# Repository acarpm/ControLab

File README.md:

## Fonctionnement de la carte ControlLab

### Vue d'ensemble

ControlLab est une carte de contrôle d'accès NFC.
Son rôle est de lire un badge NFC présenté par un utilisateur,
de vérifier son autorisation, puis de signaler le résultat
(LED + buzzer). 

```
Badge NFC
    │
    ▼
┌─────────┐    I2C     ┌──────────────────┐
│  PN532  │ ────────▶  │  ESP32-S3-MINI-1 │
│  (NFC)  │            │                  │
└─────────┘            │  • Lecture UID   │
                       │  • Vérification  │
┌─────────┐            │  • Wi-Fi / BLE   │
│  OLED   │ ◀───I2C─── │                  │
└─────────┘            └──────────────────┘
                              │        │
                         GPIO38    GPIO46
                              │        │
                        NeoPixels   Buzzer
```
                
### 1. Alimentation

La carte est alimentée via USB-C (VBUS = 5V).

- **Polyfuse F1** : protection contre les surintensités
- **TVS D6** : protection contre les surtensions ESD sur VBUS
- **AMS1117-3.3** : régulateur linéaire qui abaisse le 5V en 3.3V
  pour alimenter l'ESP32, le PN532, l'OLED et le buzzer.

USB-C (5V VBUS)
    │
   [F1] Polyfuse
    │
   [D6] TVS (protection ESD)
    │
[AMS1117-3.3] ──▶ 3V3 (ESP32, PN532, OLED, Buzzer)

### 2. Lecture NFC (PN532)

Le module PN532 est le lecteur NFC de la carte.
Il communique avec l'ESP32 via **I2C** (SDA = GPIO10, SCL = GPIO11).

Quand un badge ( tag NFC) est présenté :
1. Le PN532 détecte le champ RF et lit l'**UID** du badge
2. Il transmet l'UID à l'ESP32 via I2C

Les lignes RSTPD (GPIO11) et IRQ (GPIO10) permettent
à l'ESP32 de réinitialiser le PN532 et d'être notifié
d'une nouvelle lecture sans polling continu.

### 3. Signalisation utilisateur

#### LEDs NeoPixel (GPIO38)
3 LEDs RGB WS2812 montées en chaîne DIN → DOUT.
Elles indiquent l'état de la lecture :

| Couleur       | Signification         |
|---------------|-----------------------|
| 🟢 Vert       | Accès autorisé        |
| 🔴 Rouge      | Accès refusé          |
| 🔵 Bleu       | En attente / veille   |

#### Buzzer (GPIO46)
Buzzer actif 3.3V piloté via GPIO46 (R7 = 200Ω en série).
- 1 bip court : badge reconnu
- 2 bips : accès refusé

#### Écran OLED (J2 — I2C)
Affiche le nom de l'utilisateur ou le statut de la carte.
Lignes I2C partagées avec le PN532 .
Pull-ups 4.7kΩ maintenus à 3.3V (R5, R6).

### 5. Programmation

La carte se programme via **USB natif** (GPIO18/19 — USB D-/D+).
Aucun adaptateur UART externe nécessaire.
Pour passer en mode flash :
1. Maintenir **BOOT** (SW2 — GPIO0)
2. Appuyer sur **RESET** (SW1)
3. Relâcher BOOT

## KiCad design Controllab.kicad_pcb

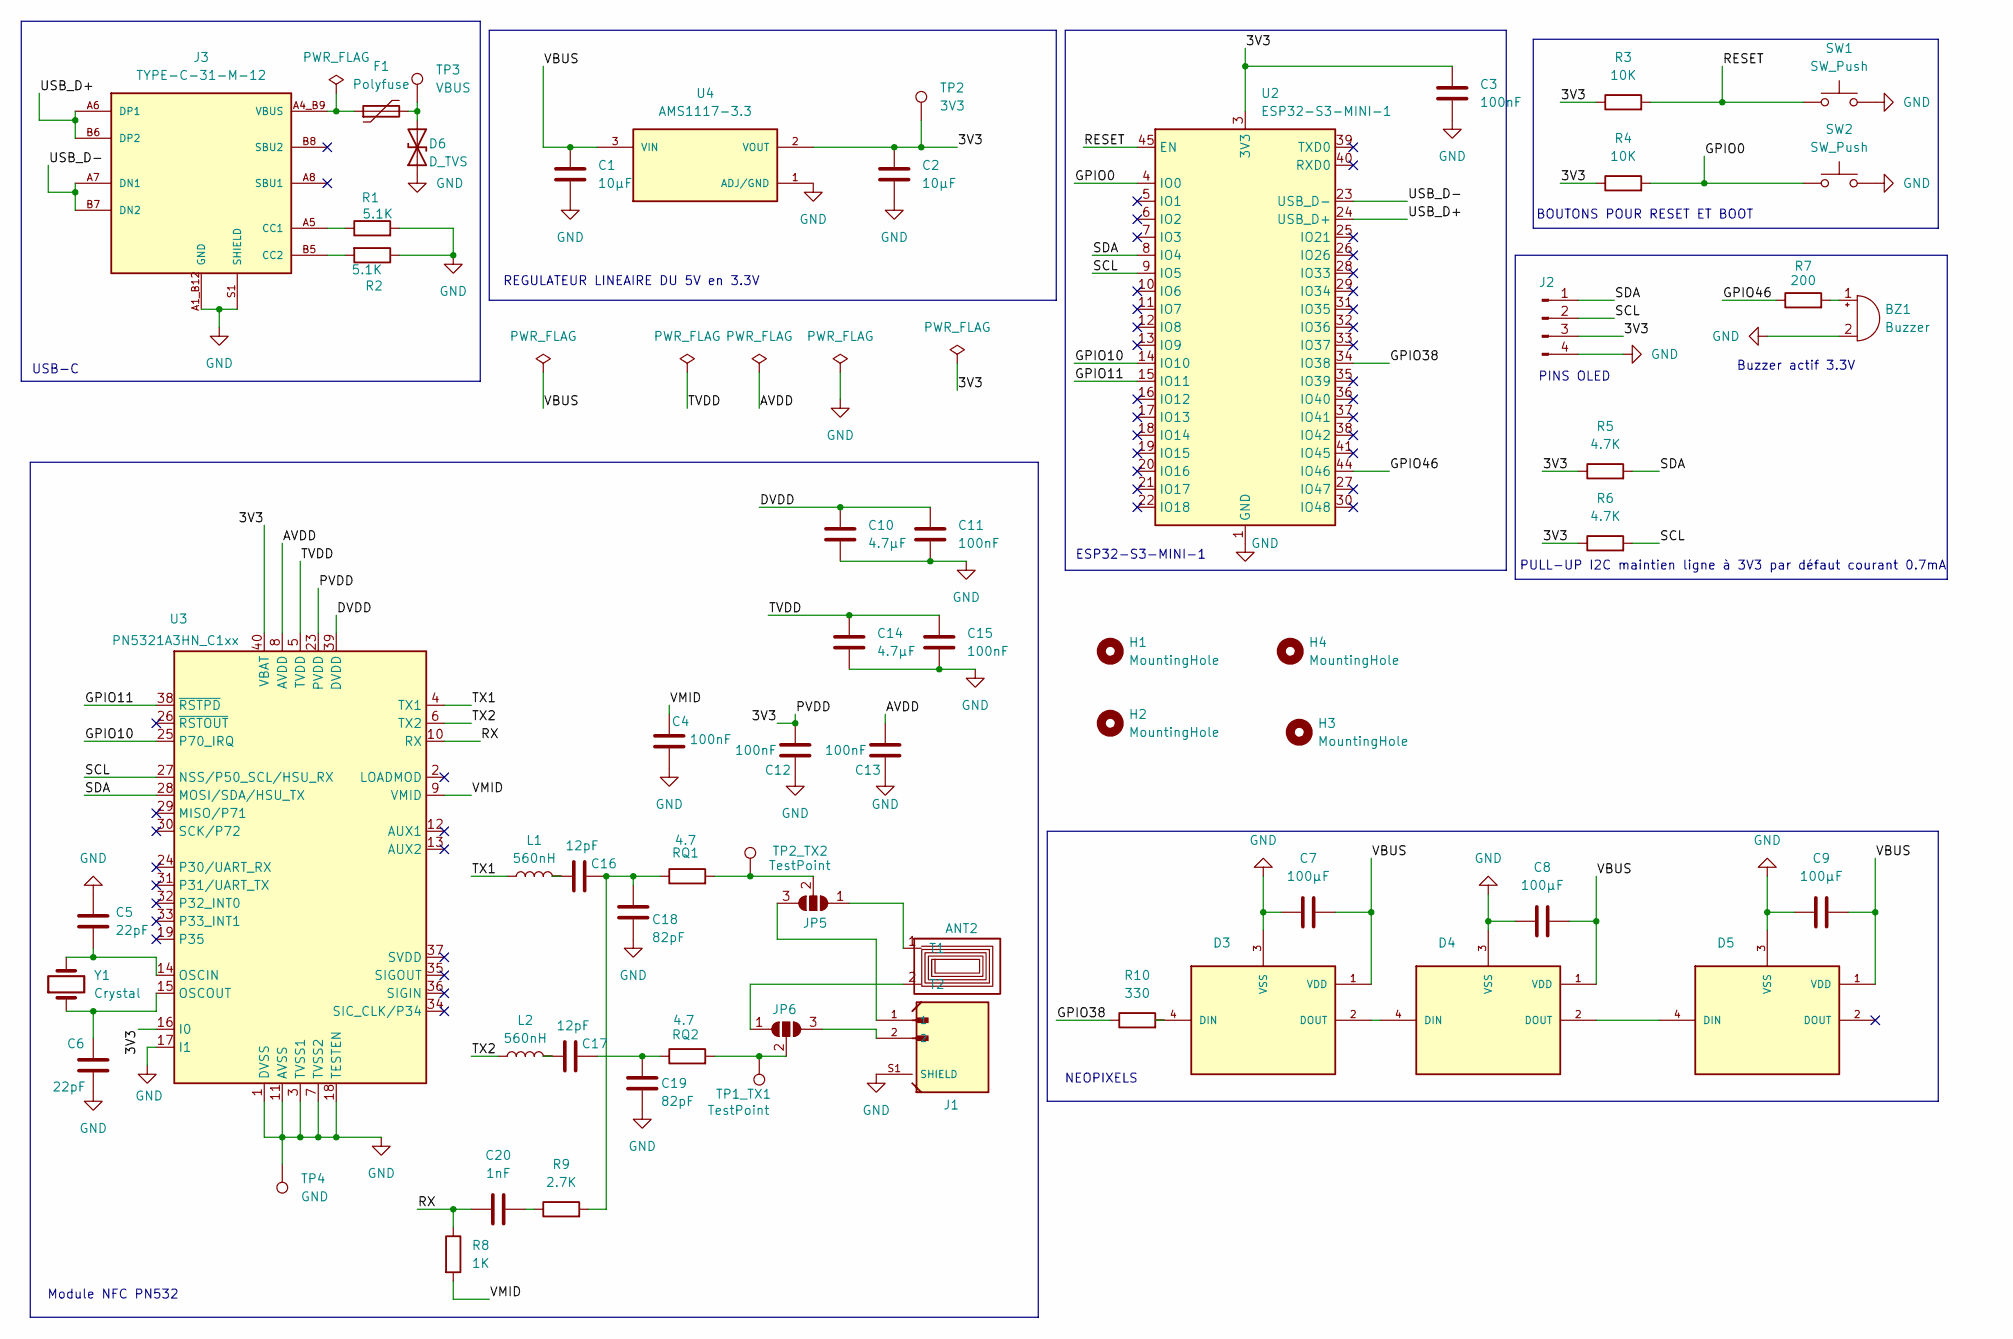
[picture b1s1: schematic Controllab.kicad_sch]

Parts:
ANT2: 13.56MHz_NFC_Antenna_Square; NFC_35x20_N5_NXP_PN532
BZ1: Buzzer; Buzzer_12x9.5RM7.6
C1, C2: 10µF; C_0603_1608Metric
C3, C4, C11, C12, C13, C15: 100nF; C_0603_1608Metric
C5, C6: 22pF; C_0603_1608Metric
C7, C8, C9: 100µF; C_0603_1608Metric
C10, C14: 4.7µF; C_0603_1608Metric
C16, C17: 12pF; C_0603_1608Metric
C18, C19: 82pF; C_0603_1608Metric
C20: 1nF; C_0603_1608Metric
D3, D4, D5: 2758; SOL320P540X170-4N; PARTREV 01
D6: D_TVS; D_SOD-123
F1: Polyfuse; Fuse_1206_3216Metric
H1, H2, H3, H4: MountingHole; MountingHole_2.1mm
J1: BM02B-GHS-TBT_LF__SN__N_; JST_BM02B-GHS-TBT_LF__SN__N_
J2: PinHeader_1x04_P2.54mm_Vertical
J3: TYPE-C-31-M-12; HRO_TYPE-C-31-M-12; PARTREV 2020.12.08
JP5, JP6: SolderJumper_3_Open; SolderJumper-3_P1.3mm_Open_Pad1.0x1.5mm
L1, L2: 560nH; L_0603_1608Metric
R1, R2: 5.1K; R_0603_1608Metric
R3, R4: 10K; R_0603_1608Metric
R5, R6: 4.7K; R_0603_1608Metric
R7: 200; R_0603_1608Metric
R8: 1K; R_0603_1608Metric
R9: 2.7K; R_0603_1608Metric
R10: 330; R_0603_1608Metric
RQ1, RQ2: 4.7; R_0603_1608Metric
SW1, SW2: SW_Push; SW_SPST_PTS645Sx43SMTR92
TP1_TX1, TP2_TX2: TestPoint; TestPoint_Pad_D1.0mm
TP2: 3V3; TestPoint_Pad_D1.0mm
TP3: VBUS; TestPoint_Pad_D1.0mm
TP4: GND; TestPoint_Pad_D1.0mm
U2: ESP32-S3-MINI-1; XCVR_ESP32-S3-MINI-1-N8
U3: PN5321A3HN_C1xx; HVQFN-40-1EP_6x6mm_P0.5mm_EP4.1x4.1mm
U4: AMS1117-3.3; SOT229P700X180-4N; PARTREV NA
Y1: Crystal; Crystal_SMD_3225-4Pin_3.2x2.5mm

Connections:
/3V3: C2.1, C3.1, C12.1, J2.3, R3.1, R4.1, R5.1, R6.1, TP2.1 (1_1), U2.3 (3V3), U3.16 (I0), U3.23 (PVDD), U3.40 (VBAT), U4.2 (VOUT)
/AVDD: C13.1, U3.8 (AVDD)
/DVDD: C10.2, C11.2, U3.39 (DVDD)
/GPIO0: R4.2, SW2.1, U2.4 (IO0)
/GPIO10: U2.14 (IO10), U3.25 (P70_IRQ)
/GPIO11: U2.15 (IO11), U3.38 (~RSTPD)
/GPIO38: R10.1, U2.34 (IO38)
/GPIO46: R7.1, U2.44 (IO46)
/RESET: R3.2, SW1.1, U2.45 (EN)
/RX: C20.1, R8.1, U3.10 (RX)
/SCL: J2.2, R6.2, U2.9 (IO5), U3.27 (NSS/P50_SCL/HSU_RX)
/SDA: J2.1, R5.2, U2.8 (IO4), U3.28 (MOSI/SDA/HSU_TX)
/TVDD: C14.2, C15.2, U3.5 (TVDD)
/TX1: L1.1, U3.4 (TX1)
/TX2: L2.1, U3.6 (TX2)
/USB_D+: J3.A6 (DP1), J3.B6 (DP2), U2.24 (USB_D+)
/USB_D-: J3.A7 (DN1), J3.B7 (DN2), U2.23 (USB_D-)
/VMID: C4.1, R8.2, U3.9 (VMID)
GND: BZ1.2 (-), C1.2, C2.2, C3.2, C4.2, C5.2, C6.2, C7.1, C8.1, C9.1, C10.1, C11.1, C12.2, C13.2, C14.1, C15.1, C18.2, C19.2, D3.3 (VSS), D4.3 (VSS), D5.3 (VSS), D6.1 (A1), J1.S1 (SHIELD), J1.S2 (SHIELD), J2.4, J3.A1_B12 (GND), J3.S1 (SHIELD), R1.2, R2.1, SW1.2, SW2.2, TP4.1 (1_1), U2.1 (GND), U2.2 (GND), U2.42 (GND), U2.43 (GND), U2.46 (GND), U2.47 (GND), U2.48 (GND), U2.49 (GND), U2.50 (GND), U2.51 (GND), U2.52 (GND), U2.53 (GND), U2.54 (GND), U2.55 (GND), U2.56 (GND), U2.57 (GND), U2.58 (GND), U2.59 (GND), U2.60 (GND), U2.61 (GND), U2.62 (GND), U2.63 (GND), U2.64 (GND), U2.65 (GND), U3.1 (DVSS), U3.3 (TVSS1), U3.7 (TVSS2), U3.11 (AVSS), U3.17 (I1), U3.18 (TESTEN), U3.41 (AVSS), U4.1 (ADJ/GND); also elsewhere on the board
unnamed: ANT2.1 (T1), JP5.1 (A)
unnamed: ANT2.2 (T2), JP6.1 (A)
unnamed: BZ1.1 (+), R7.2
unnamed: C16.1, L1.2
unnamed: C16.2, C18.1, R9.2, RQ1.1
unnamed: C17.1, L2.2
unnamed: C17.2, C19.1, RQ2.1
unnamed: C20.2, R9.1
unnamed: D3.4 (DIN), R10.2
unnamed: D3.2 (DOUT), D4.4 (DIN)
unnamed: D4.2 (DOUT), D5.4 (DIN)
unnamed: D6.2 (A2), F1.2, TP3.1 (1_1)
unnamed: J3.A5 (CC1), R1.1
unnamed: J3.B5 (CC2), R2.2
unnamed: J1.1, JP5.3 (B)
unnamed: JP5.2 (C), RQ1.2, TP2_TX2.1 (1_1)
unnamed: J1.2, JP6.3 (B)
unnamed: JP6.2 (C), RQ2.2, TP1_TX1.1 (1_1)
unnamed: C5.1, U3.14 (OSCIN), Y1.2
unnamed: C6.1, U3.15 (OSCOUT), Y1.1

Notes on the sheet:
Buzzer actif 3.3V
PINS OLED
NEOPIXELS
Module NFC PN532
ESP32-S3-MINI-1
REGULATEUR LINEAIRE DU 5V en 3.3V
USB-C
BOUTONS POUR RESET ET BOOT
PULL-UP I2C maintien ligne à 3V3 par défaut courant 0.7mA

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
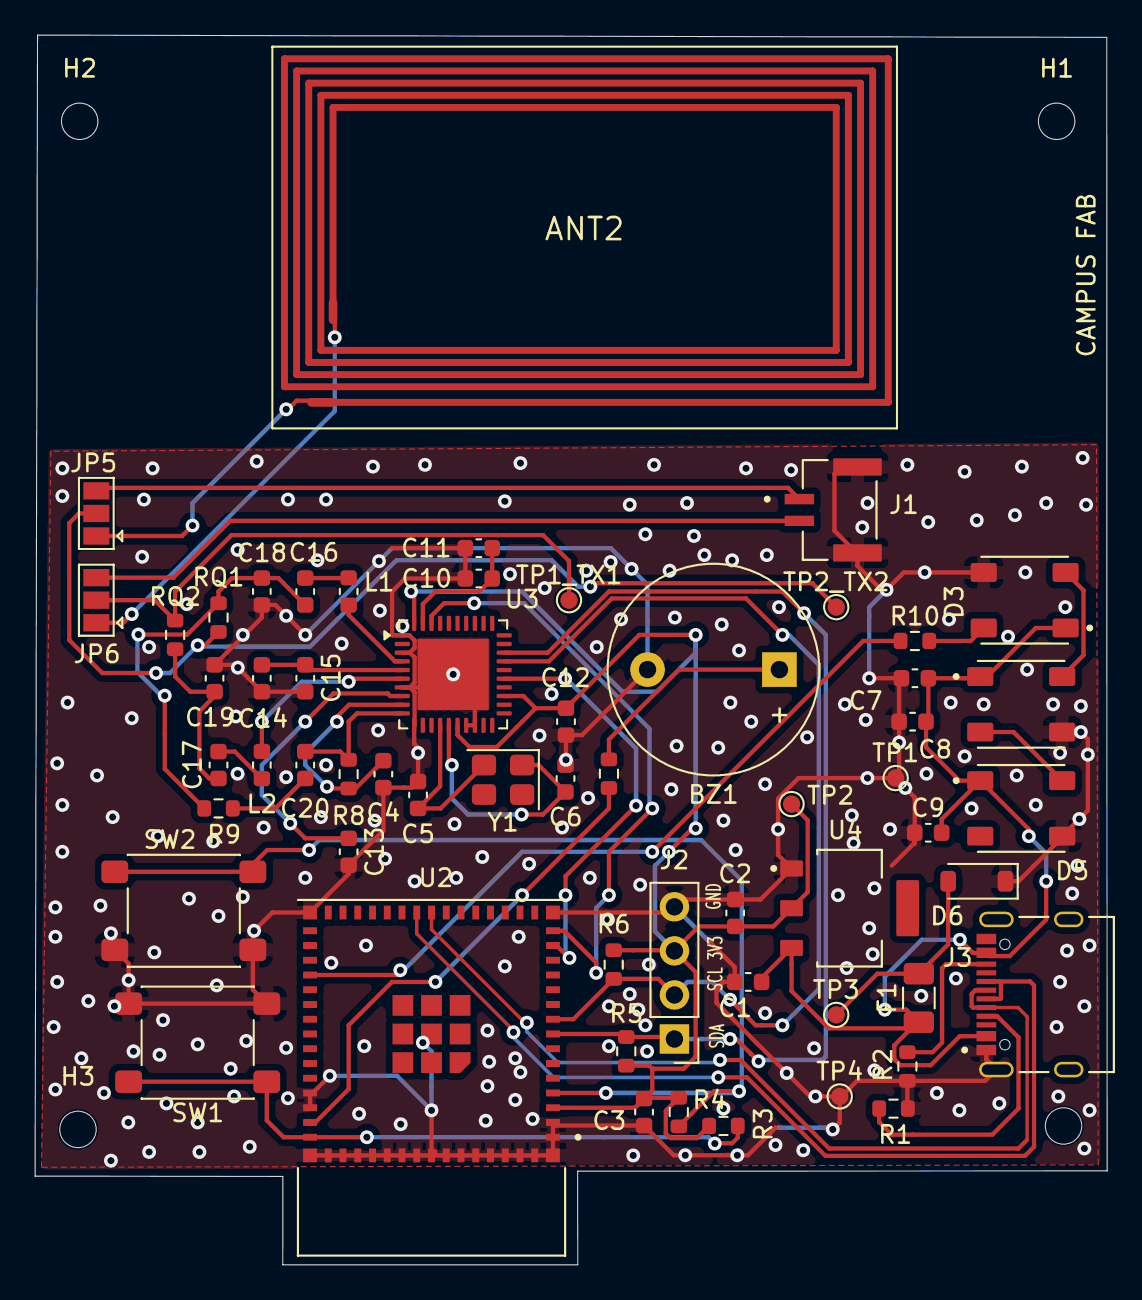
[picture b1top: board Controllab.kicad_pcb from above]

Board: 2 copper layers, 61.8 x 70.9 mm, 62 parts (0 on the bottom side), 40 nets.

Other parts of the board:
TP1: GND; TestPoint_Pad_D1.0mm

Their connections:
GND: TP1.1 (1_1); also elsewhere on the board

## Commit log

2026-06-05 programme de la badgeuse nfc
2026-06-08 La carte est prete
2026-06-08 ajout des noms sur la carte
2026-06-08 Ajout des noms sur le connecteur de l'oled
2026-06-09 Small DRC fix
2026-06-09 Add README documentation for ControlLab board
    Added detailed documentation for ControlLab NFC access control board, including overview, power supply, NFC reading, user signaling, and programming instructions.
